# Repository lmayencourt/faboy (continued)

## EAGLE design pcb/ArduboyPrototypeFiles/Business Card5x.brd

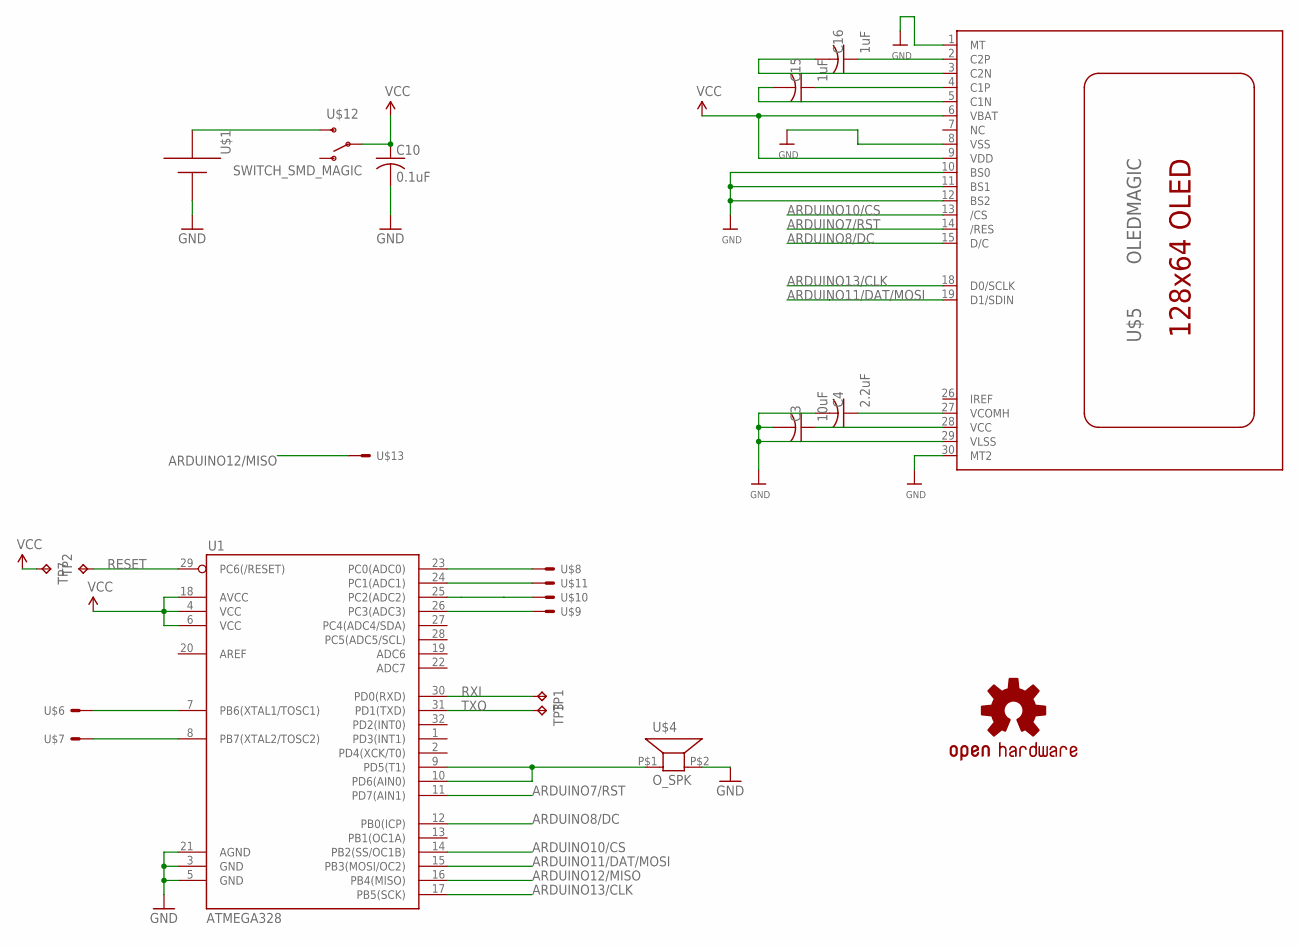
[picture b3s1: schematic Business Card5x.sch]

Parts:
C3: 10uF; 1MILCIR
C4: 2.2uF; 1MILCIR
C10: 0.1uF; 1MILCIR
C15, C16: 1uF; 1MILCIR
TP1, TP2, TP3: TPTP14R; TP14R
TP7: TPTP08SQ; TP08SQ
U1: ATMEGA328; TQFP32
U$1: 2016BAT; CR2016
U$3: OSHW-LOGOS; OSHW-LOGO-S
U$4: O_SPK
U$5: OLEDMAGIC; 1X30OLED
U$6, U$7: CAP_BUTTON; CAPBUTTON
U$8, U$9, U$10, U$11: CAP_DPAD; DPAD
U$12: SWITCH_SMD_MAGIC; SWITCH_SMD_SUNKEN
U$13: VERT_TEST

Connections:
3.3V: C10.P$1 (1), TP7.TP, U1.4 (VCC), U1.6 (VCC), U1.18 (AVCC), U$5.6 (VBAT), U$5.9 (VDD), U$12.2
ARDUINO7/RST: U1.11 (PD7(AIN1)), U$5.14 (/RES)
ARDUINO8/DC: U1.12 (PB0(ICP)), U$5.15 (D/C)
ARDUINO10/CS: U1.14 (PB2(SS/OC1B)), U$5.13 (/CS)
ARDUINO11/DAT/MOSI: U1.15 (PB3(MOSI/OC2)), U$5.19 (D1/SDIN)
ARDUINO12/MISO: U1.16 (PB4(MISO)), U$13.P$1
ARDUINO13/CLK: U1.17 (PB5(SCK)), U$5.18 (D0/SCLK)
GND: C3.P$2 (2), C4.P$2 (2), C10.P$2 (2), U1.3 (GND), U1.5 (GND), U1.21 (AGND), U$1.P$1 (+), U$4.P$2 (2), U$5.1 (MT), U$5.8 (VSS), U$5.10 (BS0), U$5.11 (BS1), U$5.12 (BS2), U$5.29 (VLSS), U$5.30 (MT2)
unnamed: U1.23 (PC0(ADC0)), U$8.P$1
unnamed: U1.24 (PC1(ADC1)), U$11.P$1
unnamed: U1.25 (PC2(ADC2)), U$10.P$1
unnamed: U1.26 (PC3(ADC3)), U$9.P$1
unnamed: C16.P$1 (1), U$5.2 (C2P)
unnamed: C16.P$2 (2), U$5.3 (C2N)
unnamed: U1.9 (PD5(T1)), U1.10 (PD6(AIN0)), U$4.P$1 (1)
unnamed: C15.P$1 (1), U$5.4 (C1P)
unnamed: C15.P$2 (2), U$5.5 (C1N)
unnamed: U1.7 (PB6(XTAL1/TOSC1)), U$6.P$1, U$6.P$2
unnamed: C3.P$1 (1), U$5.28 (VCC)
unnamed: C4.P$1 (1), U$5.27 (VCOMH)
unnamed: U1.8 (PB7(XTAL2/TOSC2)), U$7.P$1, U$7.P$2
unnamed: U$1.P$2 (-), U$12.3 (S)
RESET: TP2.TP, U1.29 (PC6(/RESET))
RXI: TP1.TP, U1.30 (PD0(RXD))
TXO: TP3.TP, U1.31 (PD1(TXD))

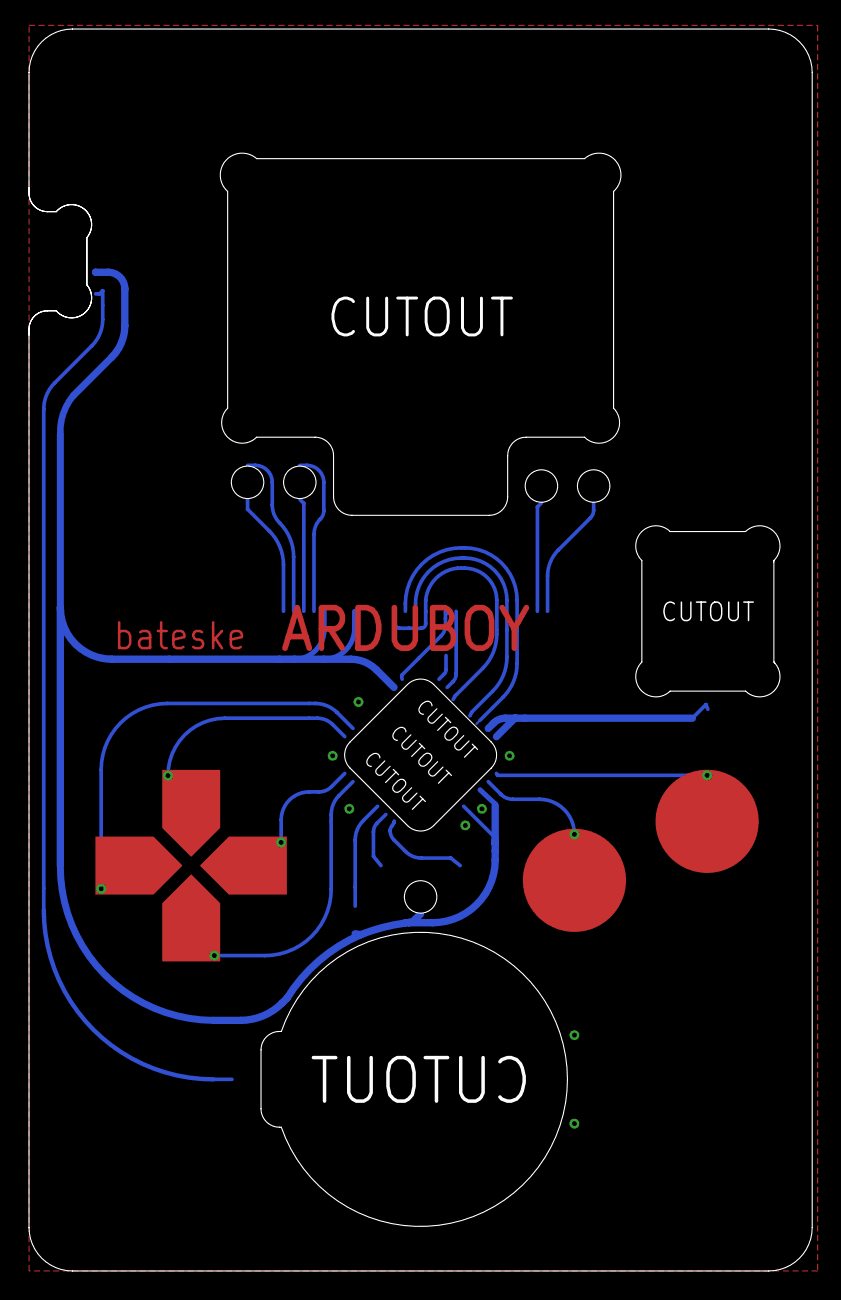
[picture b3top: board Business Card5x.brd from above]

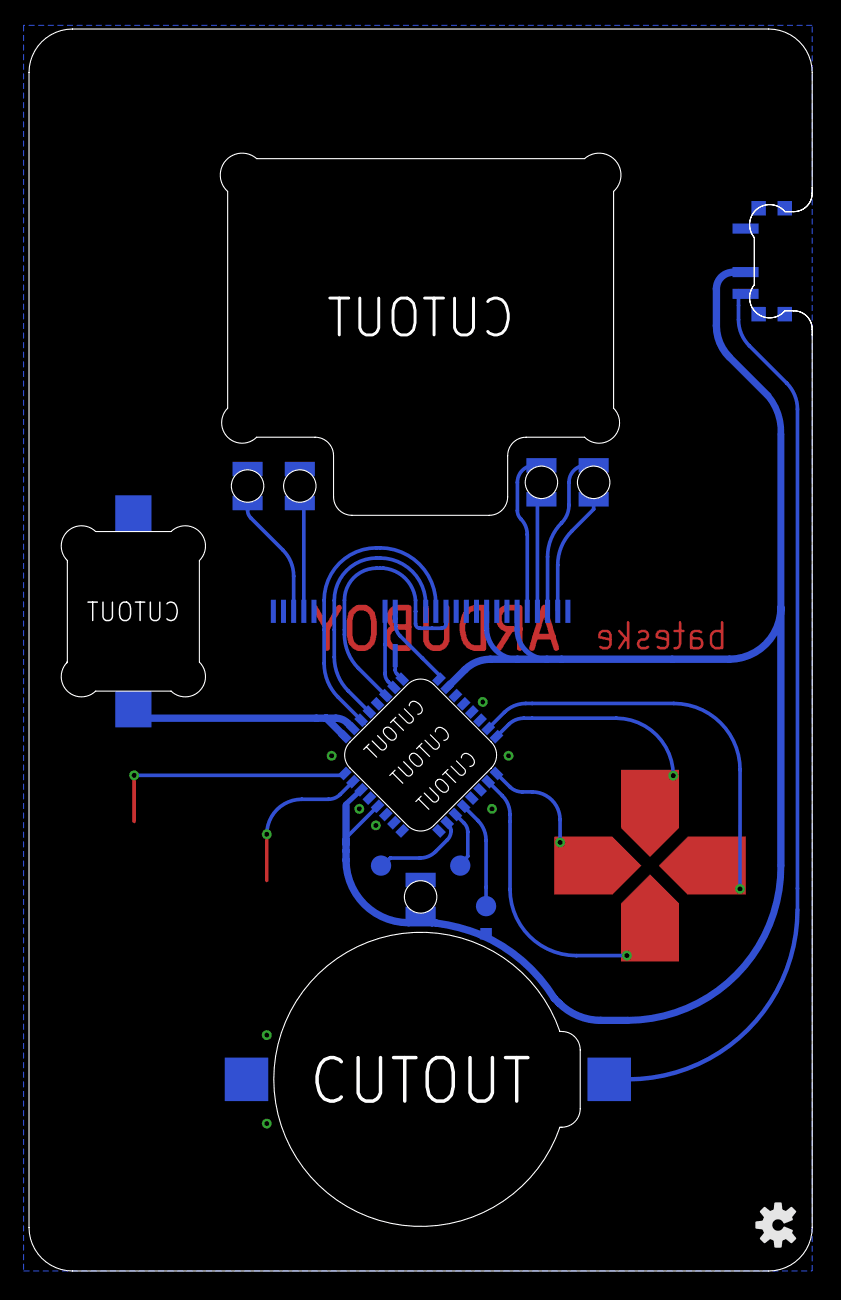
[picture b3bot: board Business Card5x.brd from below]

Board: 2 copper layers, 54.0 x 85.6 mm, 22 parts (13 on the bottom side), 25 nets.

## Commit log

2016-11-07 initial directories
2016-11-07 add BOM, datasheet and Arduboy proto files
2016-11-10 add arducard repo link
2016-11-11 schematics oled and cpu
2016-11-11 schematics leds on switch / pcb border
2016-11-15 schematics > dcdc, switch and battery / pcb > round courner
2016-11-17 schematics > rgb led / pcb > via size route
2016-11-17 pcb > start to re-arange the pin
2016-11-18 pcb > route oled, a and b pushbutton / change via size to 0.4mm / add QR code on layer 200 and 2001
2016-11-20 schematics > power path / pcb > only for 0.96 display
2016-11-20 pcb > end of routing
2016-11-20 pcb > final with silk
2016-11-23 first order
2016-11-23 change the usb connector to micro B
2016-11-29 soft > add faboy in core lib
2016-11-30 soft > lib for TeamARG game
2016-12-09 add img
2016-12-14 add games
2016-12-21 remove QR code and vcc plane fix
2017-01-05 abstract Arduboy implementation on QT
2017-01-05 Add qtboy files
2017-02-08 start the BLE version
2017-02-17 pcb ble routing
2017-02-22 ble pcb design done
